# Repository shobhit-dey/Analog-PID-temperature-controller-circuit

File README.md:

# Analog-PID-temperature-controller-circuit
An analog electronics based PID control of temperature where the feedback is taken using a thermistor and a thermoelectric cooler(TEC) is used to heat or cool actively to a setpoint. And onboard Arduino integrated for LCD monitoring. Please read the manual named "temp_ctrlr_circuit.pdf" added in this repository for a detailed guide. 

Along with this, I am also adding designs for a high power regulated voltage source that would take any unregulated high voltage input(12V or 15V) from a power supply like acopian and can give a clean, high power(several amperes of current, beyond the limit of standard zeners) regulated output. Again read the "Fan power" section from the manual to learn using this circuit.

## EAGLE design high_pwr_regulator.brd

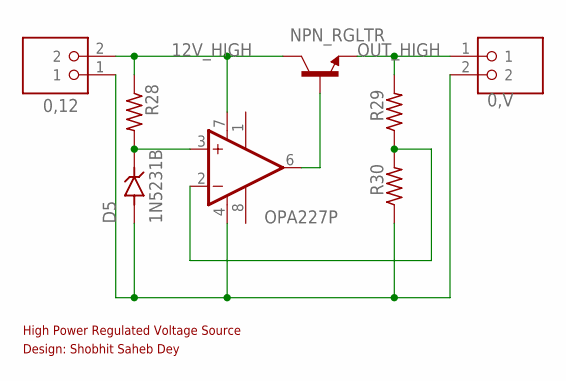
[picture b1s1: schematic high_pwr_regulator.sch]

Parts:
0,12, 0,V: 1935161; PHOENIX_1935161
D5: 1N5231B; DIOAD928W47L399D179
NPN_RGLTR: NJD2873T4G; TO229P990X238-3N
OP_FAN: OPA227P; DIL08
R28, R29, R30: R-US_0411/3V; 0411V

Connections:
12V_HIGH: 0,12.2, NPN_RGLTR.4 (C), OP_FAN.7 (V+), R28.1
GND: 0,12.1, 0,V.2, D5.A, OP_FAN.4 (V-), R30.1
unnamed: D5.C (K), OP_FAN.3 (+IN), R28.2
unnamed: OP_FAN.2 (-IN), R29.1, R30.2
unnamed: NPN_RGLTR.1 (B), OP_FAN.6 (OUT)
OUT_HIGH: 0,V.1, NPN_RGLTR.3 (E), R29.2

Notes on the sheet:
High Power Regulated Voltage Source
Design: Shobhit Saheb Dey

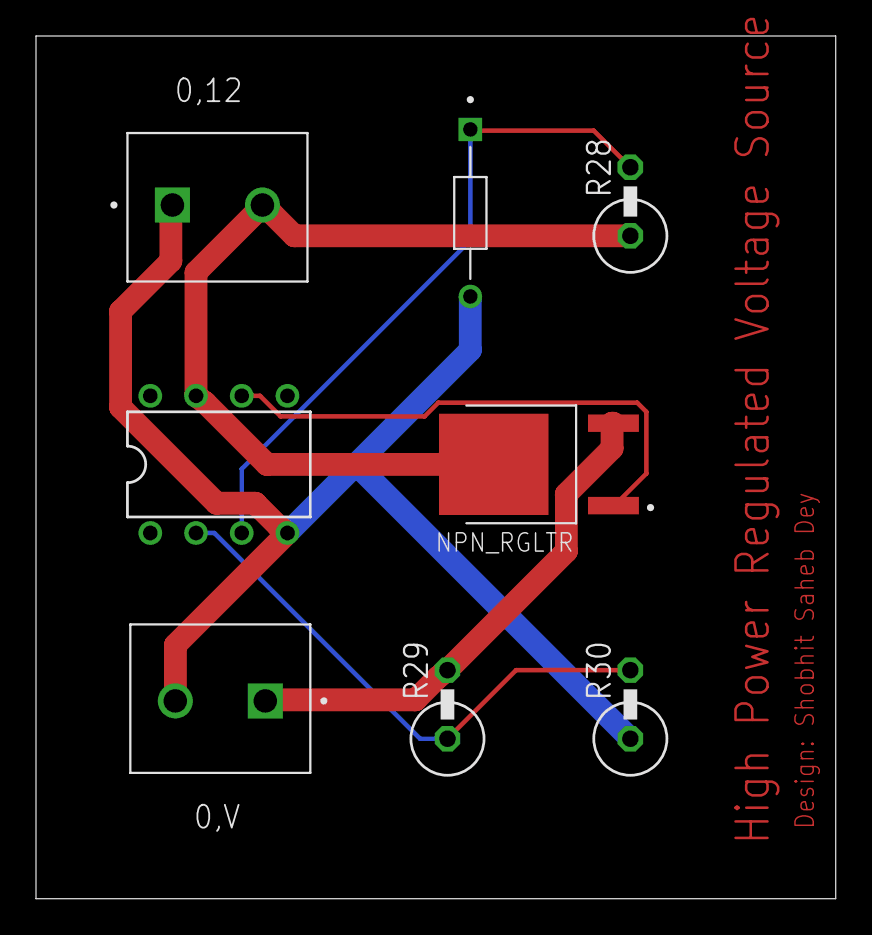
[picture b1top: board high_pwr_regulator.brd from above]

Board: 2 copper layers, 44.4 x 47.9 mm, 8 parts (0 on the bottom side), 6 nets.

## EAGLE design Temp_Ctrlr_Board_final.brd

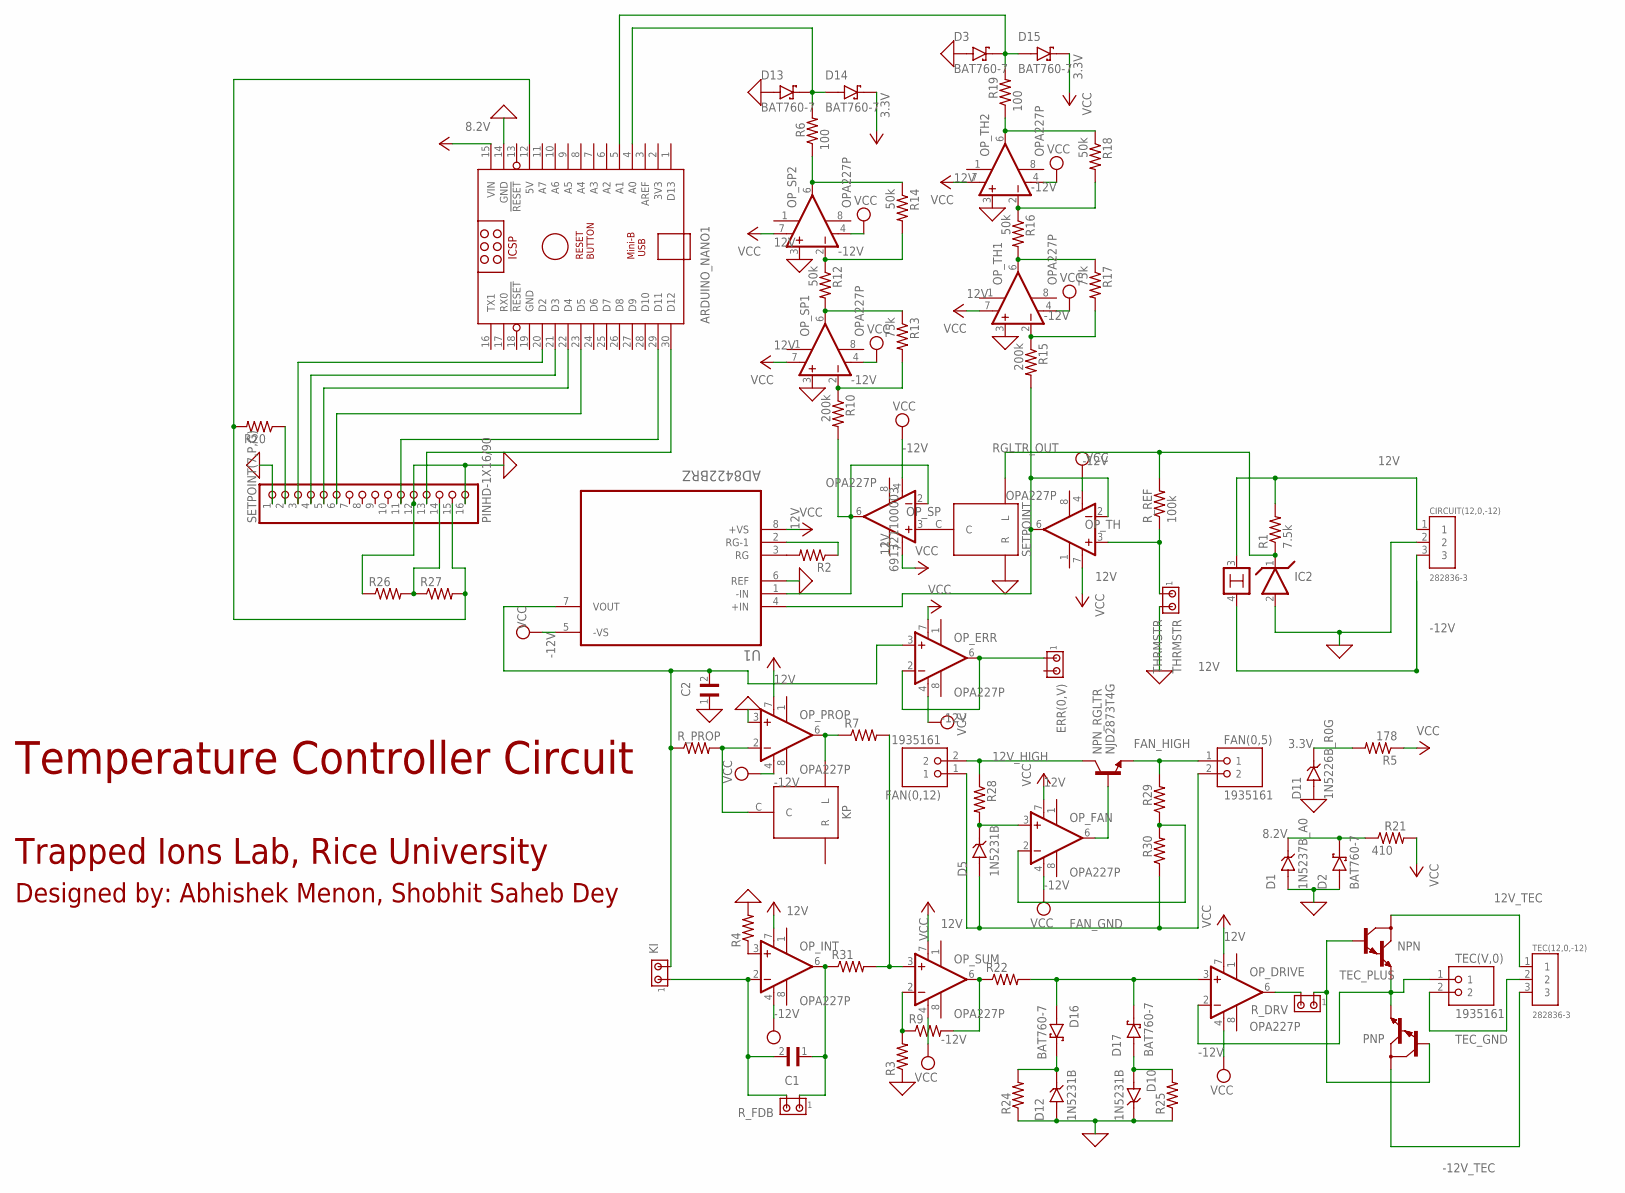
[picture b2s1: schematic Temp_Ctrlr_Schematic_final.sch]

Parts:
ARDUINO_NANO1: ARDUINO_NANO
C1, C2: C315C470J1G5TA; CAPRR254W54L381T254H466
CIRCUIT(12,0,-12): 282836-3; TE_282836-3
D1: 1N5237B_A0; DIOAD928W47L399D179
D2, D3, D13, D14, D15, D16, D17: BAT760-7; SOD2513X120N
D5, D10, D12: 1N5231B; DIOAD928W47L399D179
D11: 1N5226B_R0G; DIOAD928W47L399D179
ERR(0,V): MTA02-156; 1X2MTA
FAN(0,5), FAN(0,12): 1935161; PHOENIX_1935161
IC2: LM399H; TO39/4
KI: MTA02-156; 1X2MTA
KP: 691321100003; 691322110003
NPN: MJD122; DPAK
NPN_RGLTR: NJD2873T4G; TO229P990X238-3N
OP_DRIVE: OPA227P; DIL08
OP_ERR: OPA227P; DIL08
OP_FAN: OPA227P; DIL08
OP_INT: OPA227P; DIL08
OP_PROP: OPA227P; DIL08
OP_SP, OP_SP1, OP_SP2: OPA227P; DIL08
OP_SUM: OPA227P; DIL08
OP_TH, OP_TH1, OP_TH2: OPA227P; DIL08
PNP: MJD122; DPAK
R1: 7.5k; 0411V
R2, R3, R4, R7, R9, R20, R22, R24, R25, R26, R27, R28, R29, R30, R31: R-US_0411/3V; 0411V
R5: 178; 0411V
R6, R19: 100; 0411V
R10, R15: 200k; 0411V
R12, R14, R16, R18: 50k; 0411V
R13, R17: 75k; 0411V
R21: 410; 0411V
R_DRV: MTA02-156; 1X2MTA
R_FDB: MTA02-156; 1X2MTA
R_PROP: R-US_0411/3V; 0411V
R_REF: 100k; 0411V
SETPOINT: 691321100003; 691322110003
SETPOINT(7,P,G): PINHD-1X16/90; 1X16/90
TEC(12,0,-12): 282836-3; TE_282836-3
TEC(V,0): 1935161; PHOENIX_1935161
THRMSTR: THRMSTR; 1X2MTA
U1: AD8422BRZ; SOIC127P600X175-8N

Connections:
0: ARDUINO_NANO1.14 (GND), C2.1, CIRCUIT(12,0,-12).2, D1.A, D2.A, D3.A, D10.C (K), D11.A, D12.A, D13.A, IC2.2, OP_PROP.3 (+IN), OP_SP1.3 (+IN), OP_SP2.3 (+IN), OP_TH1.3 (+IN), OP_TH2.3 (+IN), R3.1, R4.2, R24.1, R25.1, R26.1, SETPOINT.R, SETPOINT(7,P,G).1, SETPOINT(7,P,G).12, SETPOINT(7,P,G).16, THRMSTR.2, U1.6 (REF)
3.3V: D11.C (K), D14.C (K), D15.C (K), R5.2
8.2V: ARDUINO_NANO1.15 (VIN), D1.C (K), D2.C (K), R21.1
12V: CIRCUIT(12,0,-12).1, IC2.3, OP_DRIVE.7 (V+), OP_ERR.7 (V+), OP_FAN.7 (V+), OP_INT.7 (V+), OP_PROP.7 (V+), OP_SP.7 (V+), OP_SP1.7 (V+), OP_SP2.7 (V+), OP_SUM.7 (V+), OP_TH.7 (V+), OP_TH1.7 (V+), OP_TH2.7 (V+), R1.2, R5.1, U1.8 (+VS)
12V_HIGH: FAN(0,12).2, NPN_RGLTR.4 (C), R28.1
12V_TEC: NPN.4 (C), TEC(12,0,-12).1
-12V: CIRCUIT(12,0,-12).3, IC2.4, OP_DRIVE.4 (V-), OP_ERR.4 (V-), OP_FAN.4 (V-), OP_INT.4 (V-), OP_PROP.4 (V-), OP_SP.4 (V-), OP_SP1.4 (V-), OP_SP2.4 (V-), OP_SUM.4 (V-), OP_TH.4 (V-), OP_TH1.4 (V-), OP_TH2.4 (V-), U1.5 (-VS)
-12V_TEC: PNP.4 (C), TEC(12,0,-12).3
AD1: OP_SP.2 (-IN), OP_SP.6 (OUT), R10.2, U1.1 (-IN)
AD4: OP_TH.2 (-IN), OP_TH.6 (OUT), R15.2, U1.4 (+IN)
AD7: C2.2, KI.2, OP_ERR.3 (+IN), R_PROP.1, U1.7 (VOUT)
FAN_GND: D5.A, FAN(0,5).2, FAN(0,12).1, R30.1
FAN_HIGH: FAN(0,5).1, NPN_RGLTR.3 (E), R29.2
GND: ARDUINO_NANO1.19 (GND)
unnamed: OP_INT.3 (+IN), R4.1
unnamed: OP_TH.3 (+IN), R_REF.1, THRMSTR.1
unnamed: OP_SUM.6 (OUT), R9.2, R22.1
unnamed: OP_SP.3 (+IN), SETPOINT.C
unnamed: R2.2, U1.3 (RG)
unnamed: KP.L, OP_PROP.6 (OUT), R7.1
unnamed: R2.1, U1.2 (RG-1)
unnamed: C1.2, KI.1, OP_INT.2 (-IN), R_FDB.2
unnamed: OP_SUM.3 (+IN), R7.2, R31.2
unnamed: OP_DRIVE.6 (OUT), R_DRV.2
unnamed: NPN.1 (B), PNP.1 (B), R_DRV.1
unnamed: OP_SP1.2 (-IN), R10.1, R13.2
unnamed: OP_SP1.6 (OUT), R12.2, R13.1
unnamed: OP_SUM.2 (-IN), R3.2, R9.1
unnamed: OP_SP2.2 (-IN), R12.1, R14.2
unnamed: OP_SP2.6 (OUT), R6.1, R14.1
unnamed: OP_TH1.2 (-IN), R15.1, R17.2
unnamed: OP_TH1.6 (OUT), R16.2, R17.1
unnamed: OP_TH2.2 (-IN), R16.1, R18.2
unnamed: OP_TH2.6 (OUT), R18.1, R19.1
unnamed: ARDUINO_NANO1.4 (A0), D13.C (K), D14.A, R6.2
unnamed: ARDUINO_NANO1.5 (A1), D3.C (K), D15.A, R19.2
unnamed: ERR(0,V).1, OP_ERR.2 (-IN), OP_ERR.6 (OUT)
unnamed: ARDUINO_NANO1.29 (D11), SETPOINT(7,P,G).11
unnamed: ARDUINO_NANO1.20 (D2), SETPOINT(7,P,G).3
unnamed: ARDUINO_NANO1.21 (D3), SETPOINT(7,P,G).4
unnamed: ARDUINO_NANO1.22 (D4), SETPOINT(7,P,G).5
unnamed: ARDUINO_NANO1.23 (D5), SETPOINT(7,P,G).6
unnamed: R20.1, SETPOINT(7,P,G).2
unnamed: R26.2, R27.1, SETPOINT(7,P,G).14
unnamed: ARDUINO_NANO1.12 (5V), R20.2, R27.2, SETPOINT(7,P,G).15
unnamed: ARDUINO_NANO1.30 (D12), SETPOINT(7,P,G).13
unnamed: D16.A, D17.C (K), OP_DRIVE.3 (+IN), R22.2
unnamed: D12.C (K), D16.C (K), R24.2
unnamed: D10.A, D17.A, R25.2
unnamed: C1.1, OP_INT.6 (OUT), R31.1, R_FDB.1
unnamed: KP.C, OP_PROP.2 (-IN), R_PROP.2
unnamed: D5.C (K), OP_FAN.3 (+IN), R28.2
unnamed: OP_FAN.2 (-IN), R29.1, R30.2
unnamed: NPN_RGLTR.1 (B), OP_FAN.6 (OUT)
RGLTR_OUT: IC2.1, R1.1, R_REF.2, SETPOINT.L
TEC_GND: TEC(12,0,-12).2, TEC(V,0).2
TEC_PLUS: NPN.3 (E), OP_DRIVE.2 (-IN), PNP.3 (E), TEC(V,0).1
VCC: R21.2

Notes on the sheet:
Designed by: Abhishek Menon, Shobhit Saheb Dey
Temperature Controller Circuit
Trapped Ions Lab, Rice University

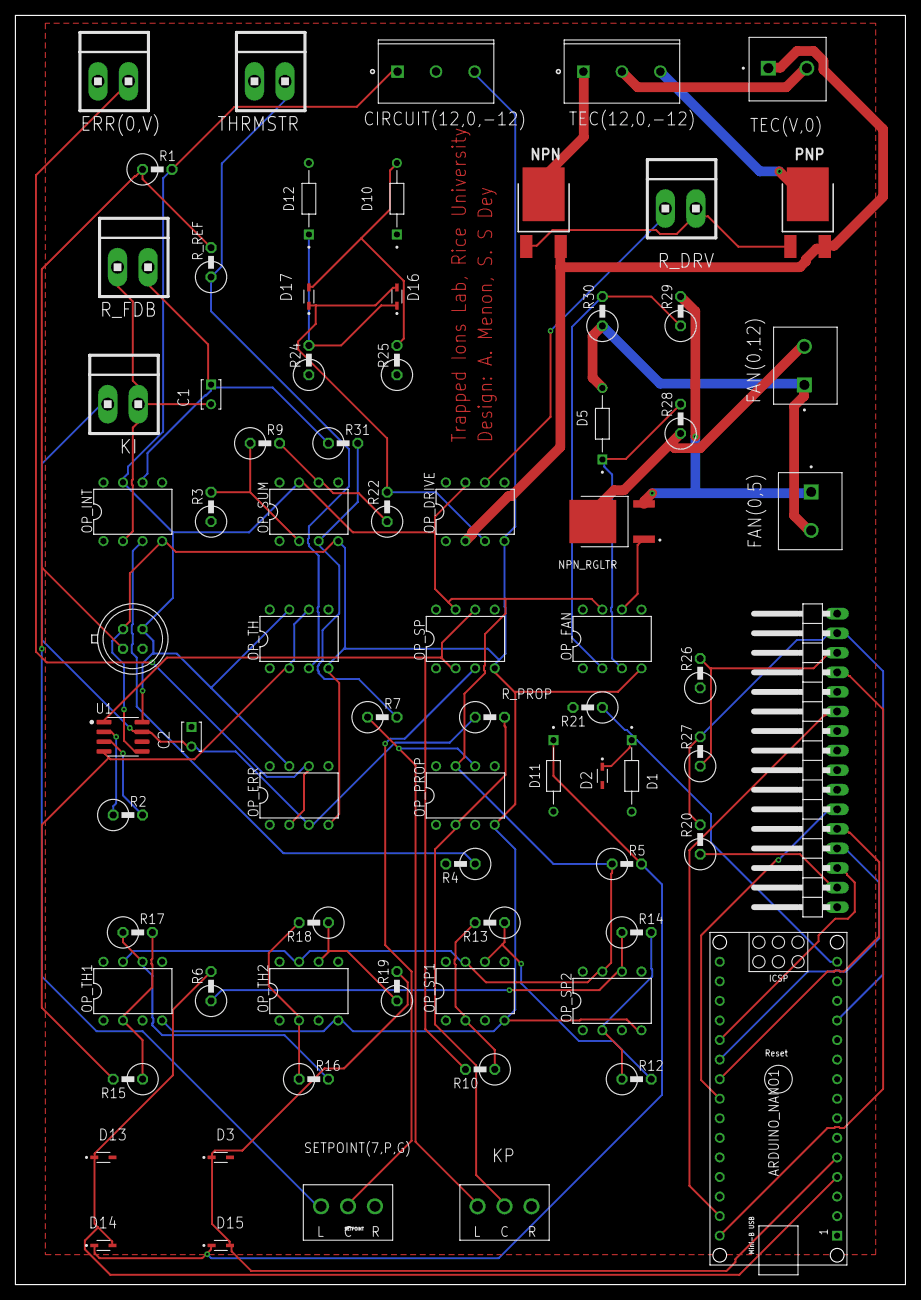
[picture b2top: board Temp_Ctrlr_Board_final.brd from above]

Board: 2 copper layers, 115.6 x 164.8 mm, 75 parts (0 on the bottom side), 56 nets.

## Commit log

2024-08-20 Rename Temperature controller circuit (2).pdf to temp_ctrlr_circuit.pdf
